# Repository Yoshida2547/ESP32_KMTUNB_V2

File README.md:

# ESP32KMUTNB_V2.0

A comprehensive ESP32-based embedded system design featuring multiple sensors, display interfaces, and USB connectivity for IoT and wearable applications.

## Overview

This project is a hardware design for an ESP32 microcontroller-based system that integrates:
- **Microcontroller**: ESP32 with USB-to-UART bridge
- **Sensors**: ADXL345 accelerometer, MAX30102 heart rate sensor, LPS22H barometric pressure sensor, HDC1080 humidity/temperature sensor
- **Display Interfaces**: TFT LCD display (3.5" 480×320 SPI) and I²C LCD module
- **Connectivity**: USB Type-C for programming and power, I²C and SPI communication buses
- **I/O**: Push buttons, RGB LED, buzzer, and GPIO headers

## Project Structure

```
ESP32KMUTNB_V2.0/
├── ESP32KMUTNB_V2.0.kicad_pro          # KiCad project file
├── ESP32KMUTNB_V2.0.kicad_sch          # Main schematic
├── ESP32KMUTNB_V2.0.kicad_pcb          # PCB layout
├── Microcontroller.kicad_sch           # Microcontroller subsystem
├── Sensor.kicad_sch                    # Sensor subsystem
├── TFT_Display.kicad_sch               # TFT display connections
├── LCD_Display.kicad_sch               # LCD display connections
├── Header.kicad_sch                    # GPIO header configuration
├── USB-to-UART Bridge.kicad_sch        # USB communication module
├── Bottons.kicad_sch                   # Button configuration
├── hardware_libs/                      # Custom libraries
│   ├── ADXL345BCCZ-RL.kicad_sym       # ADXL345 symbol
│   ├── MAX30102_Module.kicad_sym      # MAX30102 symbol
│   ├── TFT_LCD_Display.kicad_sym      # Display symbol
│   ├── footprints.pretty/             # Custom footprints
│   └── 3d_model/                      # 3D models for components
└── fp-lib-table                        # Footprint library table
```

## Key Components

| Component | Part Number | Function |
|-----------|------------|----------|
| Microcontroller | ESP32-S3 | Main processing unit |
| USB Bridge | CH340/CH341 | USB-to-UART conversion |
| Accelerometer | ADXL345BCCZ-RL | 3-axis acceleration sensing |
| Heart Rate Sensor | MAX30102 | PPG heart rate and SpO₂ measurement |
| Pressure Sensor | LPS22H | Barometric pressure and altitude |
| Humidity/Temp | HDC1080 | Temperature and humidity measurement |
| Display | ILI9488 | 3.5" TFT LCD interface |
| LED Indicators | WS2812B | RGB addressable LED |

## Schematic Organization

The design is organized into functional subsystems:

1. **Microcontroller** - ESP32 core with reset, boot circuitry, and power management
2. **USB Bridge** - CH340 UART-to-USB converter with ESD protection
3. **Sensors** - I²C sensor array with pull-up resistors and decoupling capacitors
4. **Display** - SPI TFT display interface with control signals
5. **Headers** - GPIO breakout connectors for expansion
6. **Power** - +5V input, +3.3V regulation with decoupling

## Pin Configuration

### I²C Sensors (I2C0/I2C1)
- SENSOR_SDA / SENSOR_SCL
- Connected to: ADXL345, MAX30102, LPS22H, HDC1080

### SPI Displays
- TFT LCD uses standard SPI interface
- CLK, MOSI, CS, DC, RESET signals

### GPIO Headers (J5)
- 32-pin connector with labeled I/O signals
- Supports additional peripherals and debugging

## Manufacturing Notes

- **PCB Layers**: 4-layer board
- **Design Date**: May 30, 2026
- **Revision**: A
- **3D Models**: Available for ADXL345 and MSP3520 components

## Design Files

- **KiCad Version**: 8.0.3 or later
- **Library Dependencies**: Custom symbols and footprints included
- **DXF Files**: MAX30102 module reference drawing included

## Usage

1. Open `ESP32KMUTNB_V2.0.kicad_pro` in KiCad
2. Review subsystem schematics for specific circuit details
3. Edit PCB layout in `ESP32KMUTNB_V2.0.kicad_pcb`
4. Generate production files (Gerbers, drill files) as needed

## Documentation

Refer to the individual schematic sheets for detailed circuit descriptions:
- Microcontroller configuration and boot circuitry
- Sensor connectivity and addressing
- Display interface pinout
- Power distribution and grounding strategy

## Author

Design by Surasak M. (Mark)
KMTUNB

## License

[Specify your license here]

## Contact

For questions or modifications, please contact the design team.

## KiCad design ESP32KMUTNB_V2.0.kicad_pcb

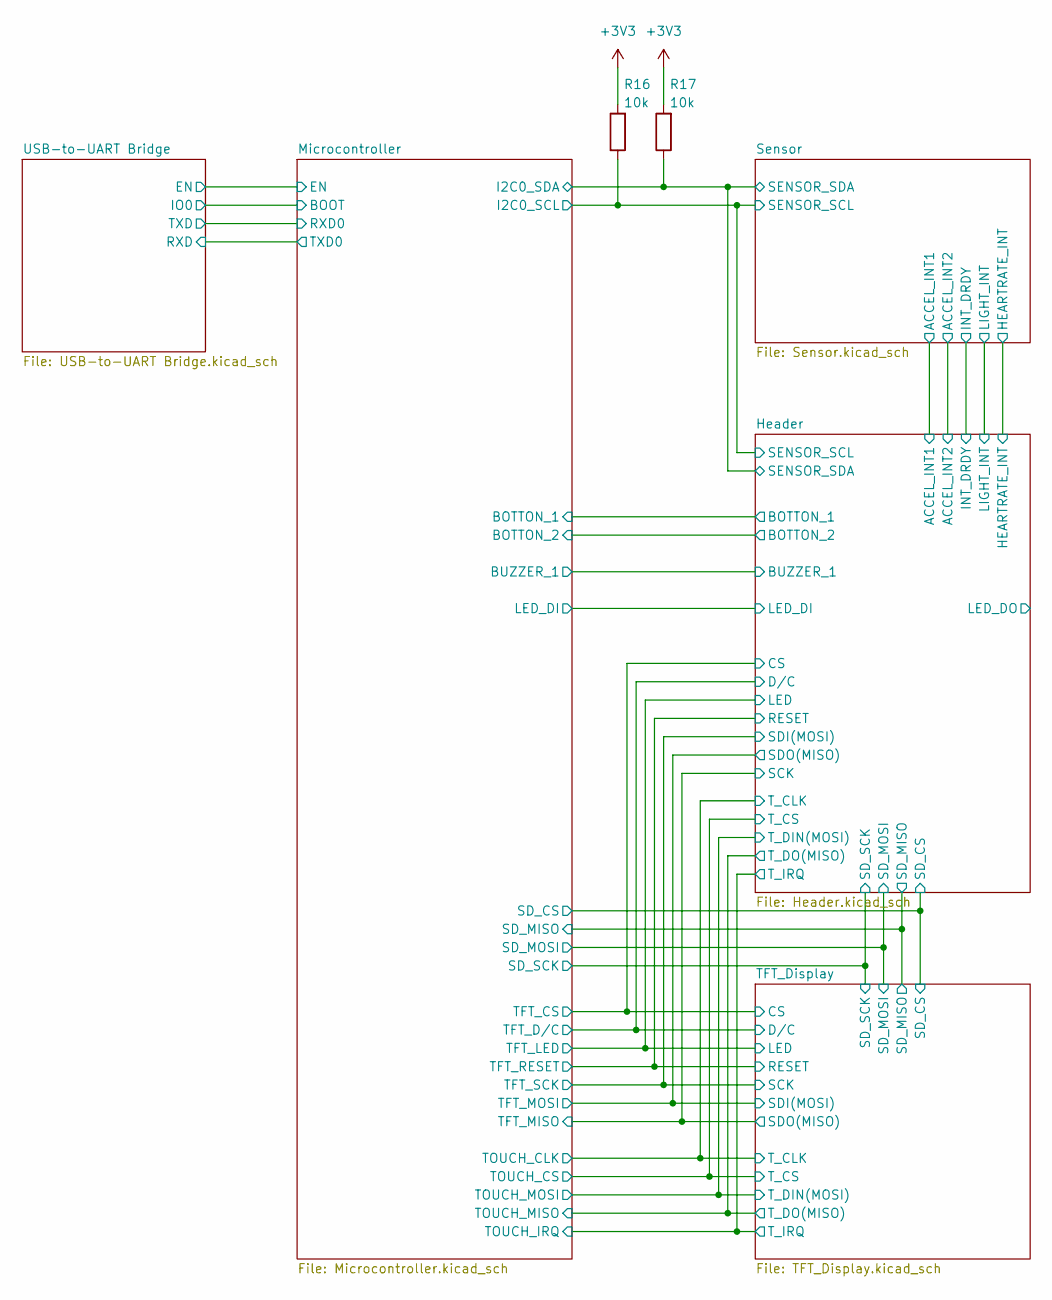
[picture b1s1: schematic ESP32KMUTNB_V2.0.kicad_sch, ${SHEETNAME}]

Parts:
R16, R17: 10k; R_0603_1608Metric_Pad0.98x0.95mm_HandSolder; MPN 0603WAF1002T5E

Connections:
+3V3: R16.2, R17.2; also elsewhere on the board
/Microcontroller/I2C0_SCL: R16.1; also elsewhere on the board
/Microcontroller/I2C0_SDA: R17.1; also elsewhere on the board

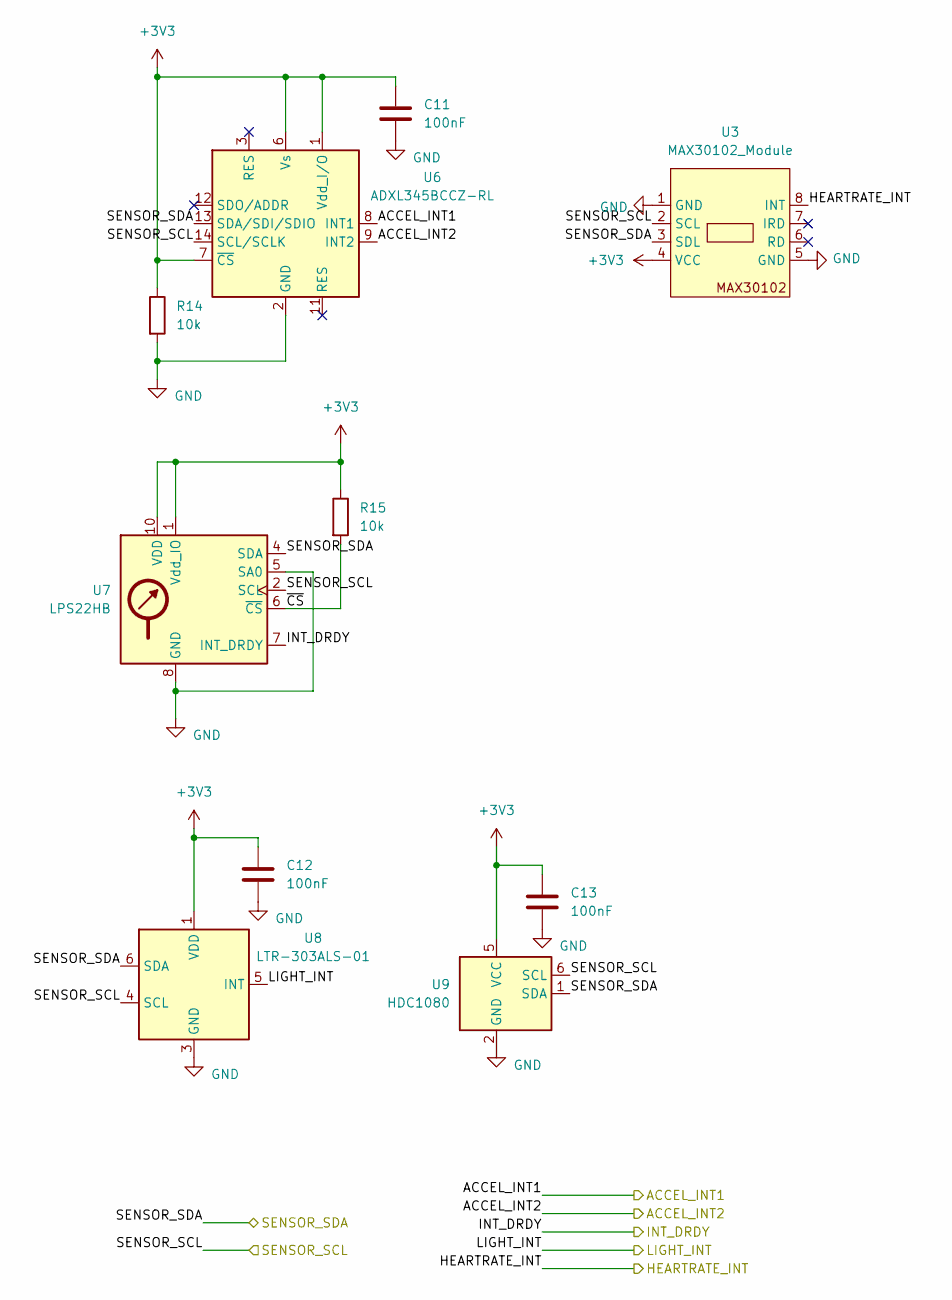
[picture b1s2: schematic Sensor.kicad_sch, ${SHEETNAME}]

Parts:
C11, C12, C13: 100nF; C_0402_1005Metric_Pad0.74x0.62mm_HandSolder; MPN CL05B104KO5NNNC
R14, R15: 10k; R_0603_1608Metric_Pad0.98x0.95mm_HandSolder; MPN 0603WAF1002T5E
U3: MAX30102_Module; MAX30102
U6: ADXL345BCCZ-RL; LGA-14_3x5mm_P0.8mm_LayoutBorder1x6y; MPN ADXL345BCCZ-RL
U7: LPS22HB; ST_HLGA-10_2x2mm_P0.5mm_LayoutBorder3x2y; MPN LPS22HBTR
U8: LTR-303ALS-01; Lite-On_LTR-303ALS-01; MPN LTR-303ALS-01
U9: HDC1080; Texas_PWSON-N6; MPN HDC1080DMBR

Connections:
+3V3: C11.1, C12.1, C13.1, R14.1, R15.1, U3.4 (VCC), U6.1 (Vdd_I/O), U6.6 (Vs), U6.7 (~CS), U7.1 (Vdd_IO), U7.10 (VDD), U8.1 (VDD), U9.5 (VCC); also elsewhere on the board
/Microcontroller/I2C0_SCL: U3.2 (SCL), U6.14 (SCL/SCLK), U7.2 (SCL), U8.4 (SCL), U9.6 (SCL); also elsewhere on the board
/Microcontroller/I2C0_SDA: U3.3 (SDL), U6.13 (SDA/SDI/SDIO), U7.4 (SDA), U8.6 (SDA), U9.1 (SDA); also elsewhere on the board
/Sensor/ACCEL_INT1: U6.8 (INT1); also elsewhere on the board
/Sensor/ACCEL_INT2: U6.9 (INT2); also elsewhere on the board
/Sensor/HEARTRATE_INT: U3.8 (INT); also elsewhere on the board
/Sensor/INT_DRDY: U7.7 (INT_DRDY); also elsewhere on the board
/Sensor/LIGHT_INT: U8.5 (INT); also elsewhere on the board
/Sensor/~CS: R15.2, U7.6 (~CS)
GND: C11.2, C12.2, C13.2, R14.2, U3.1 (GND), U3.5 (GND), U6.2 (GND), U6.4 (GND), U6.5 (GND), U7.3 (GND), U7.5 (SA0), U7.8 (GND), U7.9 (GND), U8.3 (GND), U9.2 (GND); also elsewhere on the board

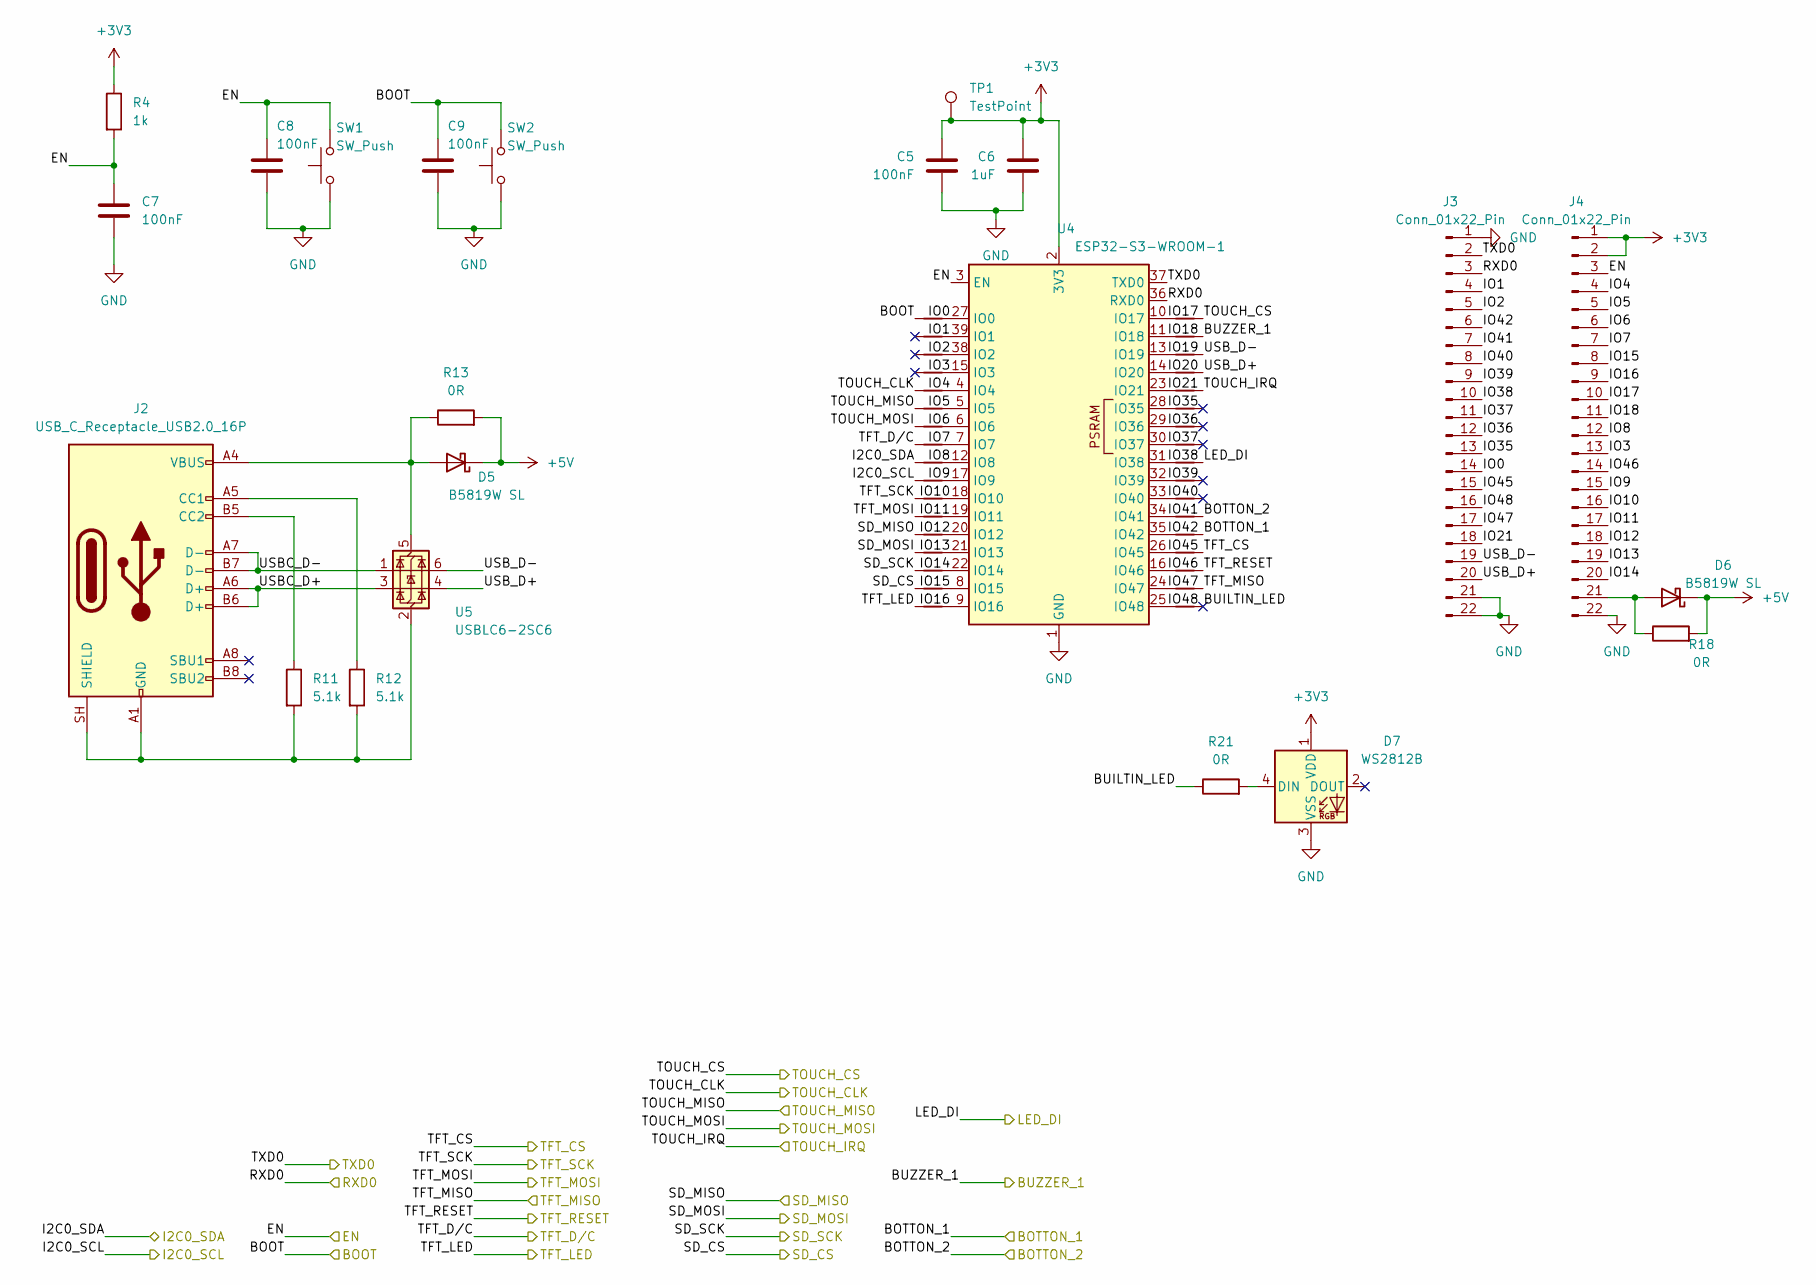
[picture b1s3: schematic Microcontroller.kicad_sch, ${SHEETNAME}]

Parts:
C5, C7, C8, C9: 100nF; C_0402_1005Metric_Pad0.74x0.62mm_HandSolder; MPN CL05B104KO5NNNC
C6: 1uF; C_0603_1608Metric_Pad1.08x0.95mm_HandSolder; MPN CL10A105KB8NNNC
D5, D6: B5819W SL; D_SOD-123; MPN B5819W SL
D7: WS2812B; LED_WS2812B_PLCC4_5.0x5.0mm_P3.2mm
J2: USB_C_Receptacle_USB2.0_16P; USB_C_Receptacle_G-Switch_GT-USB-7010ASV; MPN G-Switch GT-USB-7010ASV
J3, J4: Conn_01x22_Pin; PinSocket_1x22_P2.54mm_Vertical
NT1, NT2, NT3, NT4, NT5, NT6, NT7, NT8, NT9, NT10, NT11, NT12, NT13, NT14, NT15, NT16, NT17, NT18, NT19, NT20, NT21, NT22, NT23, NT24, NT25, NT26, NT27, NT28, NT29, NT30, NT31, NT32, NT33, NT34: NetTie_2; NetTie-2_SMD_Pad0.5mm
R4: 1k; R_0603_1608Metric_Pad0.98x0.95mm_HandSolder; MPN 0603WAF1001T5E
R11, R12: 5.1k; R_0603_1608Metric_Pad0.98x0.95mm_HandSolder; MPN 0603WAF5101T5E
R13, R18, R21: 0R; R_0603_1608Metric_Pad0.98x0.95mm_HandSolder; MPN 0603WAF0000T5E
SW1, SW2: SW_Push; SW_SPST_B3U-1000P; MPN XUNPU TS-1088-AR02016
TP1: TestPoint; TestPoint_Pad_D1.5mm
U4: ESP32-S3-WROOM-1; MPN ESP32-S3-WROOM-1-N8R2
U5: USBLC6-2SC6; SOT-23-6; MPN USBLC6-2SC6

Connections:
+3V3: C5.1, C6.1, D7.1 (VDD), J4.1, J4.2, R4.1, TP1.1 (1_1), U4.2 (3V3); also elsewhere on the board
+5V: D5.1 (K), D6.1 (K), R13.2, R18.2; also elsewhere on the board
/Header/LED_DI: NT22.2; also elsewhere on the board
/Microcontroller/BOOT: C9.1, NT14.1, SW2.2; also elsewhere on the board
/Microcontroller/BOTTON_1: NT27.2; also elsewhere on the board
/Microcontroller/BOTTON_2: NT25.2; also elsewhere on the board
/Microcontroller/BUILTIN_LED: NT32.2, R21.1
/Microcontroller/BUZZER_1: NT28.2; also elsewhere on the board
/Microcontroller/EN: C7.1, C8.1, J4.3, R4.2, SW1.2, U4.3 (EN); also elsewhere on the board
/Microcontroller/I2C0_SCL: NT6.1; also elsewhere on the board
/Microcontroller/I2C0_SDA: NT5.1; also elsewhere on the board
/Microcontroller/IO0: J3.14, NT14.2, U4.27 (IO0)
/Microcontroller/IO1: J3.4, NT15.2 (2_2), U4.39 (IO1)
/Microcontroller/IO2: J3.5, NT16.2 (2_2), U4.38 (IO2)
/Microcontroller/IO3: J4.13, NT17.2 (2_2), U4.15 (IO3)
/Microcontroller/IO4: J4.4, NT1.2, U4.4 (IO4)
/Microcontroller/IO5: J4.5, NT2.2, U4.5 (IO5)
/Microcontroller/IO6: J4.6, NT3.2, U4.6 (IO6)
/Microcontroller/IO7: J4.7, NT4.2, U4.7 (IO7)
/Microcontroller/IO8: J4.12, NT5.2, U4.12 (IO8)
/Microcontroller/IO9: J4.15, NT6.2, U4.17 (IO9)
/Microcontroller/IO10: J4.16, NT7.2, U4.18 (IO10)
/Microcontroller/IO11: J4.17, NT8.2, U4.19 (IO11)
/Microcontroller/IO12: J4.18, NT9.2, U4.20 (IO12)
/Microcontroller/IO13: J4.19, NT10.2, U4.21 (IO13)
/Microcontroller/IO14: J4.20, NT11.2, U4.22 (IO14)
/Microcontroller/IO15: J4.8, NT12.2, U4.8 (IO15)
/Microcontroller/IO16: J4.9, NT13.2, U4.9 (IO16)
/Microcontroller/IO17: J4.10, NT26.1, U4.10 (IO17)
/Microcontroller/IO18: J4.11, NT28.1, U4.11 (IO18)
/Microcontroller/IO19: NT33.1, U4.13 (IO19)
/Microcontroller/IO20: NT34.1, U4.14 (IO20)
/Microcontroller/IO21: J3.18, NT18.1, U4.23 (IO21)
/Microcontroller/IO35: J3.13, NT19.1 (1_1), U4.28 (IO35)
/Microcontroller/IO36: J3.12, NT20.1 (1_1), U4.29 (IO36)
/Microcontroller/IO37: J3.11, NT21.1 (1_1), U4.30 (IO37)
/Microcontroller/IO38: J3.10, NT22.1, U4.31 (IO38)
/Microcontroller/IO39: J3.9, NT23.1 (1_1), U4.32 (IO39)
/Microcontroller/IO40: J3.8, NT24.1 (1_1), U4.33 (IO40)
/Microcontroller/IO41: J3.7, NT25.1, U4.34 (IO41)
/Microcontroller/IO42: J3.6, NT27.1, U4.35 (IO42)
/Microcontroller/IO45: J3.15, NT29.1, U4.26 (IO45)
/Microcontroller/IO46: J4.14, NT30.1, U4.16 (IO46)
/Microcontroller/IO47: J3.17, NT31.1, U4.24 (IO47)
/Microcontroller/IO48: J3.16, NT32.1, U4.25 (IO48)
/Microcontroller/RXD0: J3.3, U4.36 (RXD0); also elsewhere on the board
/Microcontroller/SD_CS: NT12.1; also elsewhere on the board
/Microcontroller/SD_MISO: NT9.1; also elsewhere on the board
/Microcontroller/SD_MOSI: NT10.1; also elsewhere on the board
/Microcontroller/SD_SCK: NT11.1; also elsewhere on the board
/Microcontroller/TFT_CS: NT29.2; also elsewhere on the board
/Microcontroller/TFT_D/C: NT4.1; also elsewhere on the board
/Microcontroller/TFT_LED: NT13.1; also elsewhere on the board
/Microcontroller/TFT_MISO: NT31.2; also elsewhere on the board
/Microcontroller/TFT_MOSI: NT8.1; also elsewhere on the board
/Microcontroller/TFT_RESET: NT30.2; also elsewhere on the board
/Microcontroller/TFT_SCK: NT7.1; also elsewhere on the board
/Microcontroller/TOUCH_CLK: NT1.1; also elsewhere on the board
/Microcontroller/TOUCH_CS: NT26.2; also elsewhere on the board
/Microcontroller/TOUCH_IRQ: NT18.2; also elsewhere on the board
/Microcontroller/TOUCH_MISO: NT2.1; also elsewhere on the board
/Microcontroller/TOUCH_MOSI: NT3.1; also elsewhere on the board
/Microcontroller/TXD0: J3.2, U4.37 (TXD0); also elsewhere on the board
/Microcontroller/USBC_D+: J2.A6 (D+), J2.B6 (D+), U5.3 (I/O2)
/Microcontroller/USBC_D-: J2.A7 (D-), J2.B7 (D-), U5.1 (I/O1)
/Microcontroller/USB_D+: J3.20, NT34.2, U5.4 (I/O2)
/Microcontroller/USB_D-: J3.19, NT33.2, U5.6 (I/O1)
GND: C5.2, C6.2, C7.2, C8.2, C9.2, D7.3 (VSS), J3.1, J3.21, J3.22, J4.22, SW1.1, SW2.1, U4.1 (GND), U4.40 (GND), U4.41 (GND); also elsewhere on the board
unnamed: D5.2 (A), J2.A4 (VBUS), J2.A9 (VBUS), J2.B4 (VBUS), J2.B9 (VBUS), R13.1, U5.5 (VBUS)
unnamed: D6.2 (A), J4.21, R18.1
unnamed: D7.4 (DIN), R21.2
unnamed: J2.A5 (CC1), R12.1
unnamed: J2.B5 (CC2), R11.1
unnamed: J2.A1 (GND), J2.A12 (GND), J2.B1 (GND), J2.B12 (GND), J2.SH (SHIELD), R11.2, R12.2, U5.2 (GND)

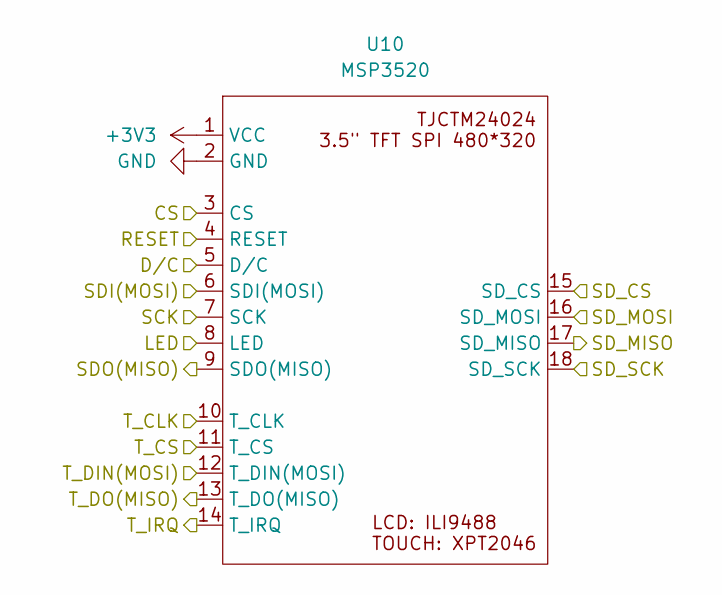
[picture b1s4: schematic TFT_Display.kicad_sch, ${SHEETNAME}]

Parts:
U10: MSP3520; MSP3520_WithoutHole

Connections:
+3V3: U10.1 (VCC); also elsewhere on the board
/Microcontroller/SD_CS: U10.15 (SD_CS); also elsewhere on the board
/Microcontroller/SD_MISO: U10.17 (SD_MISO); also elsewhere on the board
/Microcontroller/SD_MOSI: U10.16 (SD_MOSI); also elsewhere on the board
/Microcontroller/SD_SCK: U10.18 (SD_SCK); also elsewhere on the board
/Microcontroller/TFT_CS: U10.3 (CS); also elsewhere on the board
/Microcontroller/TFT_D/C: U10.5 (D/C); also elsewhere on the board
/Microcontroller/TFT_LED: U10.8 (LED); also elsewhere on the board
/Microcontroller/TFT_MISO: U10.9 (SDO(MISO)); also elsewhere on the board
/Microcontroller/TFT_MOSI: U10.6 (SDI(MOSI)); also elsewhere on the board
/Microcontroller/TFT_RESET: U10.4 (RESET); also elsewhere on the board
/Microcontroller/TFT_SCK: U10.7 (SCK); also elsewhere on the board
/Microcontroller/TOUCH_CLK: U10.10 (T_CLK); also elsewhere on the board
/Microcontroller/TOUCH_CS: U10.11 (T_CS); also elsewhere on the board
/Microcontroller/TOUCH_IRQ: U10.14 (T_IRQ); also elsewhere on the board
/Microcontroller/TOUCH_MISO: U10.13 (T_DO(MISO)); also elsewhere on the board
/Microcontroller/TOUCH_MOSI: U10.12 (T_DIN(MOSI)); also elsewhere on the board
GND: U10.2 (GND); also elsewhere on the board

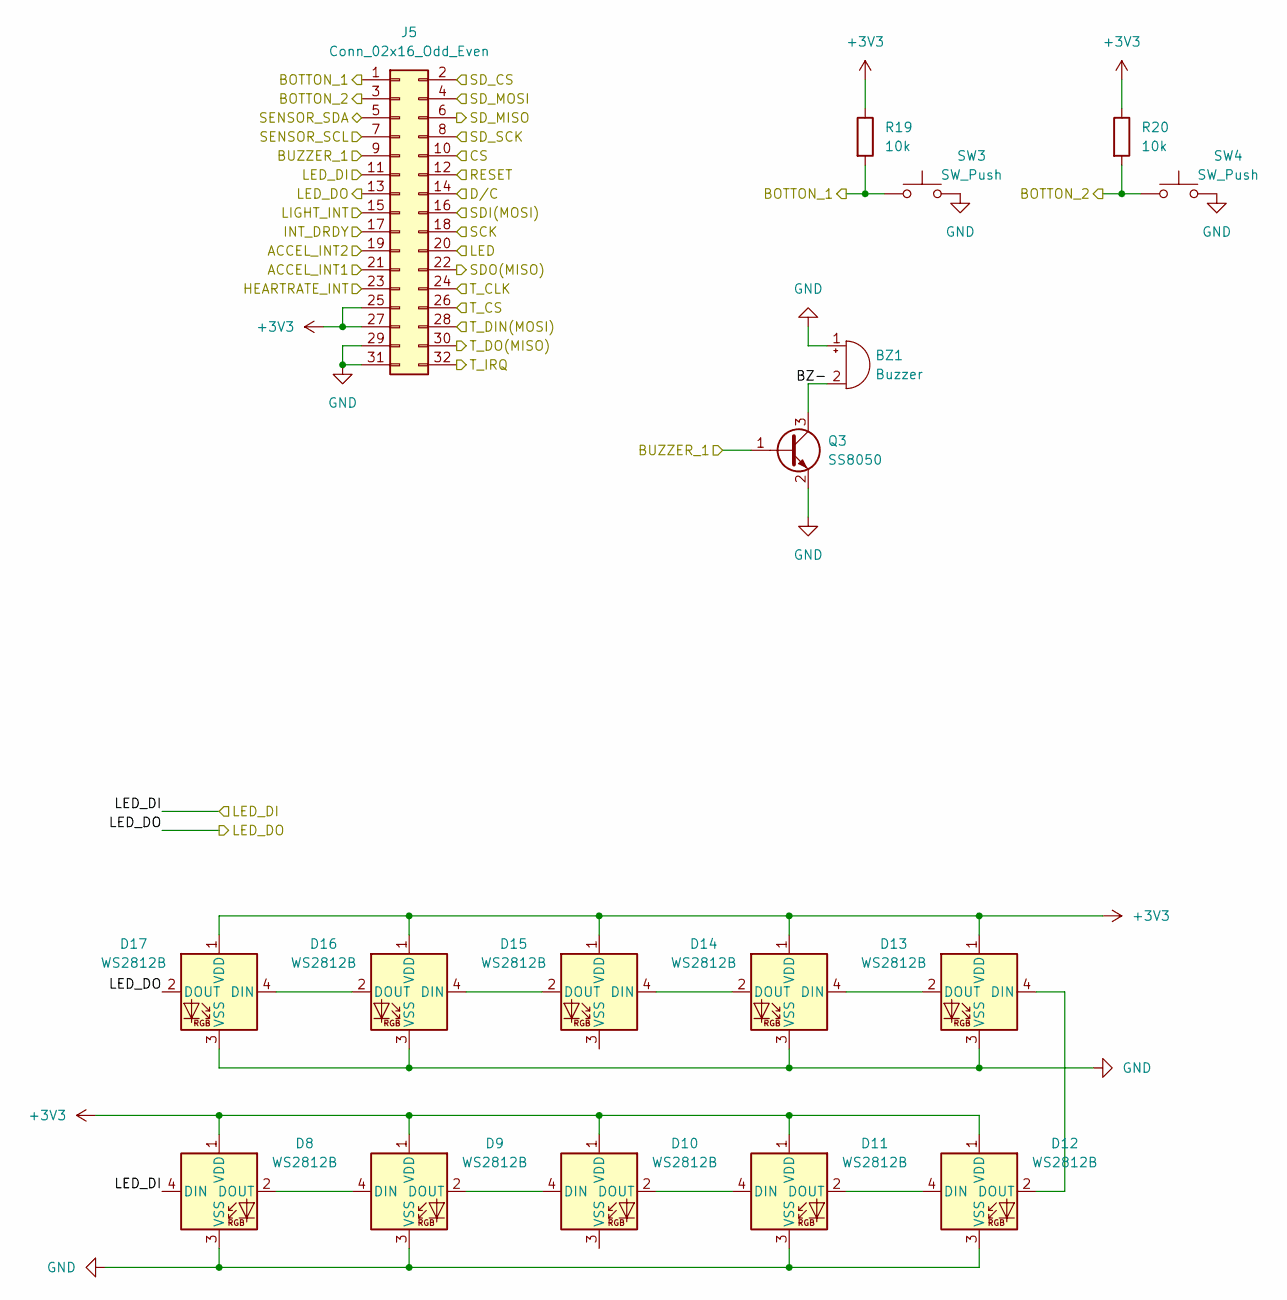
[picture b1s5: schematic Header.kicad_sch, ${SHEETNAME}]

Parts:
BZ1: Buzzer; Huaneng MLT-9650; MPN MLT-9650
D8, D9, D10, D11, D12, D13, D14, D15, D16, D17: WS2812B; LED_WS2812B_PLCC4_5.0x5.0mm_P3.2mm
J5: Conn_02x16_Odd_Even; PinHeader_2x16_P2.54mm_Vertical
Q3: SS8050; SOT-23; MPN S8050 J3Y(RANGE:200-350)
R19, R20: 10k; R_0603_1608Metric_Pad0.98x0.95mm_HandSolder; MPN 0603WAF1002T5E
SW3, SW4: SW_Push; SW_Push_1TS009xxxx-xxxx-xxxx_6x6x5mm; MPN 1TS009A-1800-5000-CT

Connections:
+3V3: D8.1 (VDD), D9.1 (VDD), D10.1 (VDD), D11.1 (VDD), D12.1 (VDD), D13.1 (VDD), D14.1 (VDD), D15.1 (VDD), D16.1 (VDD), D17.1 (VDD), J5.25, J5.27, R19.1, R20.1; also elsewhere on the board
/Header/BZ-: BZ1.2 (-), Q3.3 (C)
/Header/LED_DI: D8.4 (DIN), J5.11; also elsewhere on the board
/Header/LED_DO: D17.2 (DOUT), J5.13
/Microcontroller/BOTTON_1: J5.1, R19.2, SW3.1; also elsewhere on the board
/Microcontroller/BOTTON_2: J5.3, R20.2, SW4.1; also elsewhere on the board
/Microcontroller/BUZZER_1: J5.9, Q3.1 (B); also elsewhere on the board
/Microcontroller/I2C0_SCL: J5.7; also elsewhere on the board
/Microcontroller/I2C0_SDA: J5.5; also elsewhere on the board
/Microcontroller/SD_CS: J5.2; also elsewhere on the board
/Microcontroller/SD_MISO: J5.6; also elsewhere on the board
/Microcontroller/SD_MOSI: J5.4; also elsewhere on the board
/Microcontroller/SD_SCK: J5.8; also elsewhere on the board
/Microcontroller/TFT_CS: J5.10; also elsewhere on the board
/Microcontroller/TFT_D/C: J5.14; also elsewhere on the board
/Microcontroller/TFT_LED: J5.20; also elsewhere on the board
/Microcontroller/TFT_MISO: J5.18; also elsewhere on the board
/Microcontroller/TFT_MOSI: J5.22; also elsewhere on the board
/Microcontroller/TFT_RESET: J5.12; also elsewhere on the board
/Microcontroller/TFT_SCK: J5.16; also elsewhere on the board
/Microcontroller/TOUCH_CLK: J5.24; also elsewhere on the board
/Microcontroller/TOUCH_CS: J5.26; also elsewhere on the board
/Microcontroller/TOUCH_IRQ: J5.32; also elsewhere on the board
/Microcontroller/TOUCH_MISO: J5.30; also elsewhere on the board
/Microcontroller/TOUCH_MOSI: J5.28; also elsewhere on the board
/Sensor/ACCEL_INT1: J5.21; also elsewhere on the board
/Sensor/ACCEL_INT2: J5.19; also elsewhere on the board
/Sensor/HEARTRATE_INT: J5.23; also elsewhere on the board
/Sensor/INT_DRDY: J5.17; also elsewhere on the board
/Sensor/LIGHT_INT: J5.15; also elsewhere on the board
GND: BZ1.1 (+), D8.3 (VSS), D9.3 (VSS), D11.3 (VSS), D12.3 (VSS), D13.3 (VSS), D14.3 (VSS), D16.3 (VSS), D17.3 (VSS), J5.29, J5.31, Q3.2 (E), SW3.2, SW4.2; also elsewhere on the board
unnamed: D8.2 (DOUT), D9.4 (DIN)
unnamed: D9.2 (DOUT), D10.4 (DIN)
unnamed: D10.2 (DOUT), D11.4 (DIN)
unnamed: D11.2 (DOUT), D12.4 (DIN)
unnamed: D12.2 (DOUT), D13.4 (DIN)
unnamed: D13.2 (DOUT), D14.4 (DIN)
unnamed: D14.2 (DOUT), D15.4 (DIN)
unnamed: D15.2 (DOUT), D16.4 (DIN)
unnamed: D16.2 (DOUT), D17.4 (DIN)

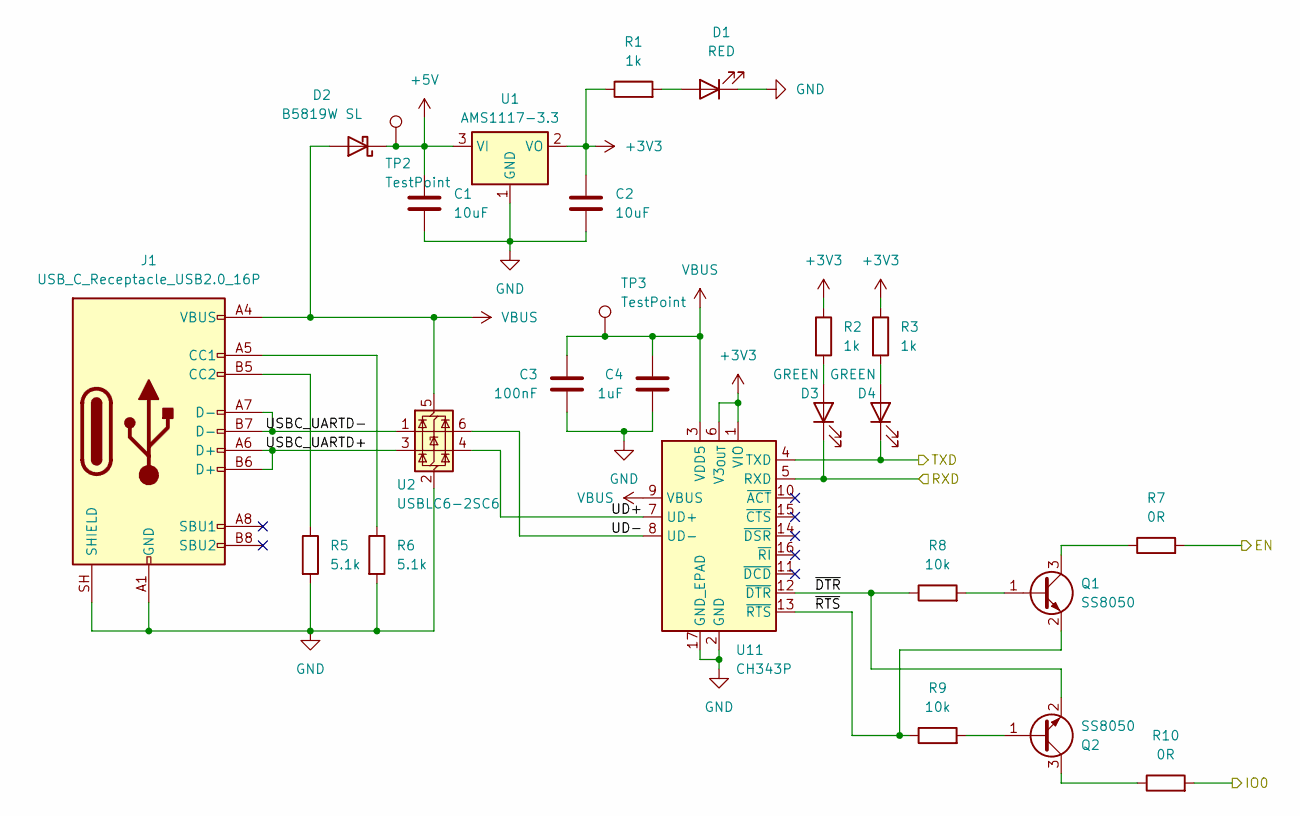
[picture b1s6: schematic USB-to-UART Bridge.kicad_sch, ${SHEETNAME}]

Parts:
C1, C2: 10uF; C_0603_1608Metric_Pad1.08x0.95mm_HandSolder; MPN CL10A106KP8NNNC
C3: 100nF; C_0402_1005Metric_Pad0.74x0.62mm_HandSolder; MPN CL05B104KO5NNNC
C4: 1uF; C_0603_1608Metric_Pad1.08x0.95mm_HandSolder; MPN CL10A105KB8NNNC
D1: RED; LED_0805_2012Metric_Pad1.15x1.40mm_HandSolder; MPN NCD0805R1
D2: B5819W SL; D_SOD-123; MPN B5819W SL
D3, D4: GREEN; LED_0805_2012Metric_Pad1.15x1.40mm_HandSolder; MPN KT-0805G
J1: USB_C_Receptacle_USB2.0_16P; USB_C_Receptacle_G-Switch_GT-USB-7010ASV; MPN G-Switch GT-USB-7010ASV
Q1, Q2: SS8050; SOT-23; MPN S8050 J3Y(RANGE:200-350)
R1, R2, R3: 1k; R_0603_1608Metric_Pad0.98x0.95mm_HandSolder; MPN 0603WAF1001T5E
R5, R6: 5.1k; R_0603_1608Metric_Pad0.98x0.95mm_HandSolder; MPN 0603WAF5101T5E
R7, R10: 0R; R_0603_1608Metric_Pad0.98x0.95mm_HandSolder; MPN 0603WAF0000T5E
R8, R9: 10k; R_0603_1608Metric_Pad0.98x0.95mm_HandSolder; MPN 0603WAF1002T5E
TP2, TP3: TestPoint; TestPoint_Pad_D1.5mm
U1: AMS1117-3.3; SOT-223-3_TabPin2; MPN AMS1117-3.3
U2: USBLC6-2SC6; SOT-23-6; MPN USBLC6-2SC6
U11: CH343P; WCH_QFN-16-1EP_3x3mm_P0.5mm_EP1.8x1.8mm; MPN CH343P

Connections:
+3V3: C2.1, R1.1, R2.1, R3.1, U1.2 (VO), U11.1 (VIO), U11.6 (V3_{OUT}); also elsewhere on the board
+5V: C1.1, D2.1 (K), TP2.1 (1_1), U1.3 (VI); also elsewhere on the board
/Microcontroller/BOOT: R10.2; also elsewhere on the board
/Microcontroller/EN: R7.2; also elsewhere on the board
/Microcontroller/RXD0: D4.1 (K), U11.4 (TXD); also elsewhere on the board
/Microcontroller/TXD0: D3.1 (K), U11.5 (RXD); also elsewhere on the board
/USB-to-UART Bridge/UD+: U2.4 (I/O2), U11.7 (UD+)
/USB-to-UART Bridge/UD-: U2.6 (I/O1), U11.8 (UD-)
/USB-to-UART Bridge/USBC_UARTD+: J1.A6 (D+), J1.B6 (D+), U2.3 (I/O2)
/USB-to-UART Bridge/USBC_UARTD-: J1.A7 (D-), J1.B7 (D-), U2.1 (I/O1)
/USB-to-UART Bridge/~DTR: Q2.2 (E), R8.1, U11.12 (~DTR)
/USB-to-UART Bridge/~RTS: Q1.2 (E), R9.1, U11.13 (~RTS)
GND: C1.2, C2.2, C3.2, C4.2, D1.1 (K), J1.A1 (GND), J1.A12 (GND), J1.B1 (GND), J1.B12 (GND), J1.SH (SHIELD), R5.2, R6.2, U1.1 (GND), U2.2 (GND), U11.2 (GND), U11.17 (GND_EPAD); also elsewhere on the board
unnamed: D1.2 (A), R1.2
unnamed: D3.2 (A), R2.2
unnamed: D4.2 (A), R3.2
unnamed: J1.A5 (CC1), R6.1
unnamed: J1.B5 (CC2), R5.1
unnamed: Q1.1 (B), R8.2
unnamed: Q1.3 (C), R7.1
unnamed: Q2.1 (B), R9.2
unnamed: Q2.3 (C), R10.1
VBUS: C3.1, C4.1, D2.2 (A), J1.A4 (VBUS), J1.A9 (VBUS), J1.B4 (VBUS), J1.B9 (VBUS), TP3.1 (1_1), U2.5 (VBUS), U11.3 (VDD5), U11.9 (VBUS)

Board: 2 copper layers, 111 parts (0 on the bottom side), 107 nets, no tracks yet.
